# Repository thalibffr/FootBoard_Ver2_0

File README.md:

# Footboard ICHIRO Ver2.0

New Board Design for Foot Pressure of humanoid robot ICHIRO ITS

In this new design analog sensor data readings use ads1262

[Top view]

[Bottom view]

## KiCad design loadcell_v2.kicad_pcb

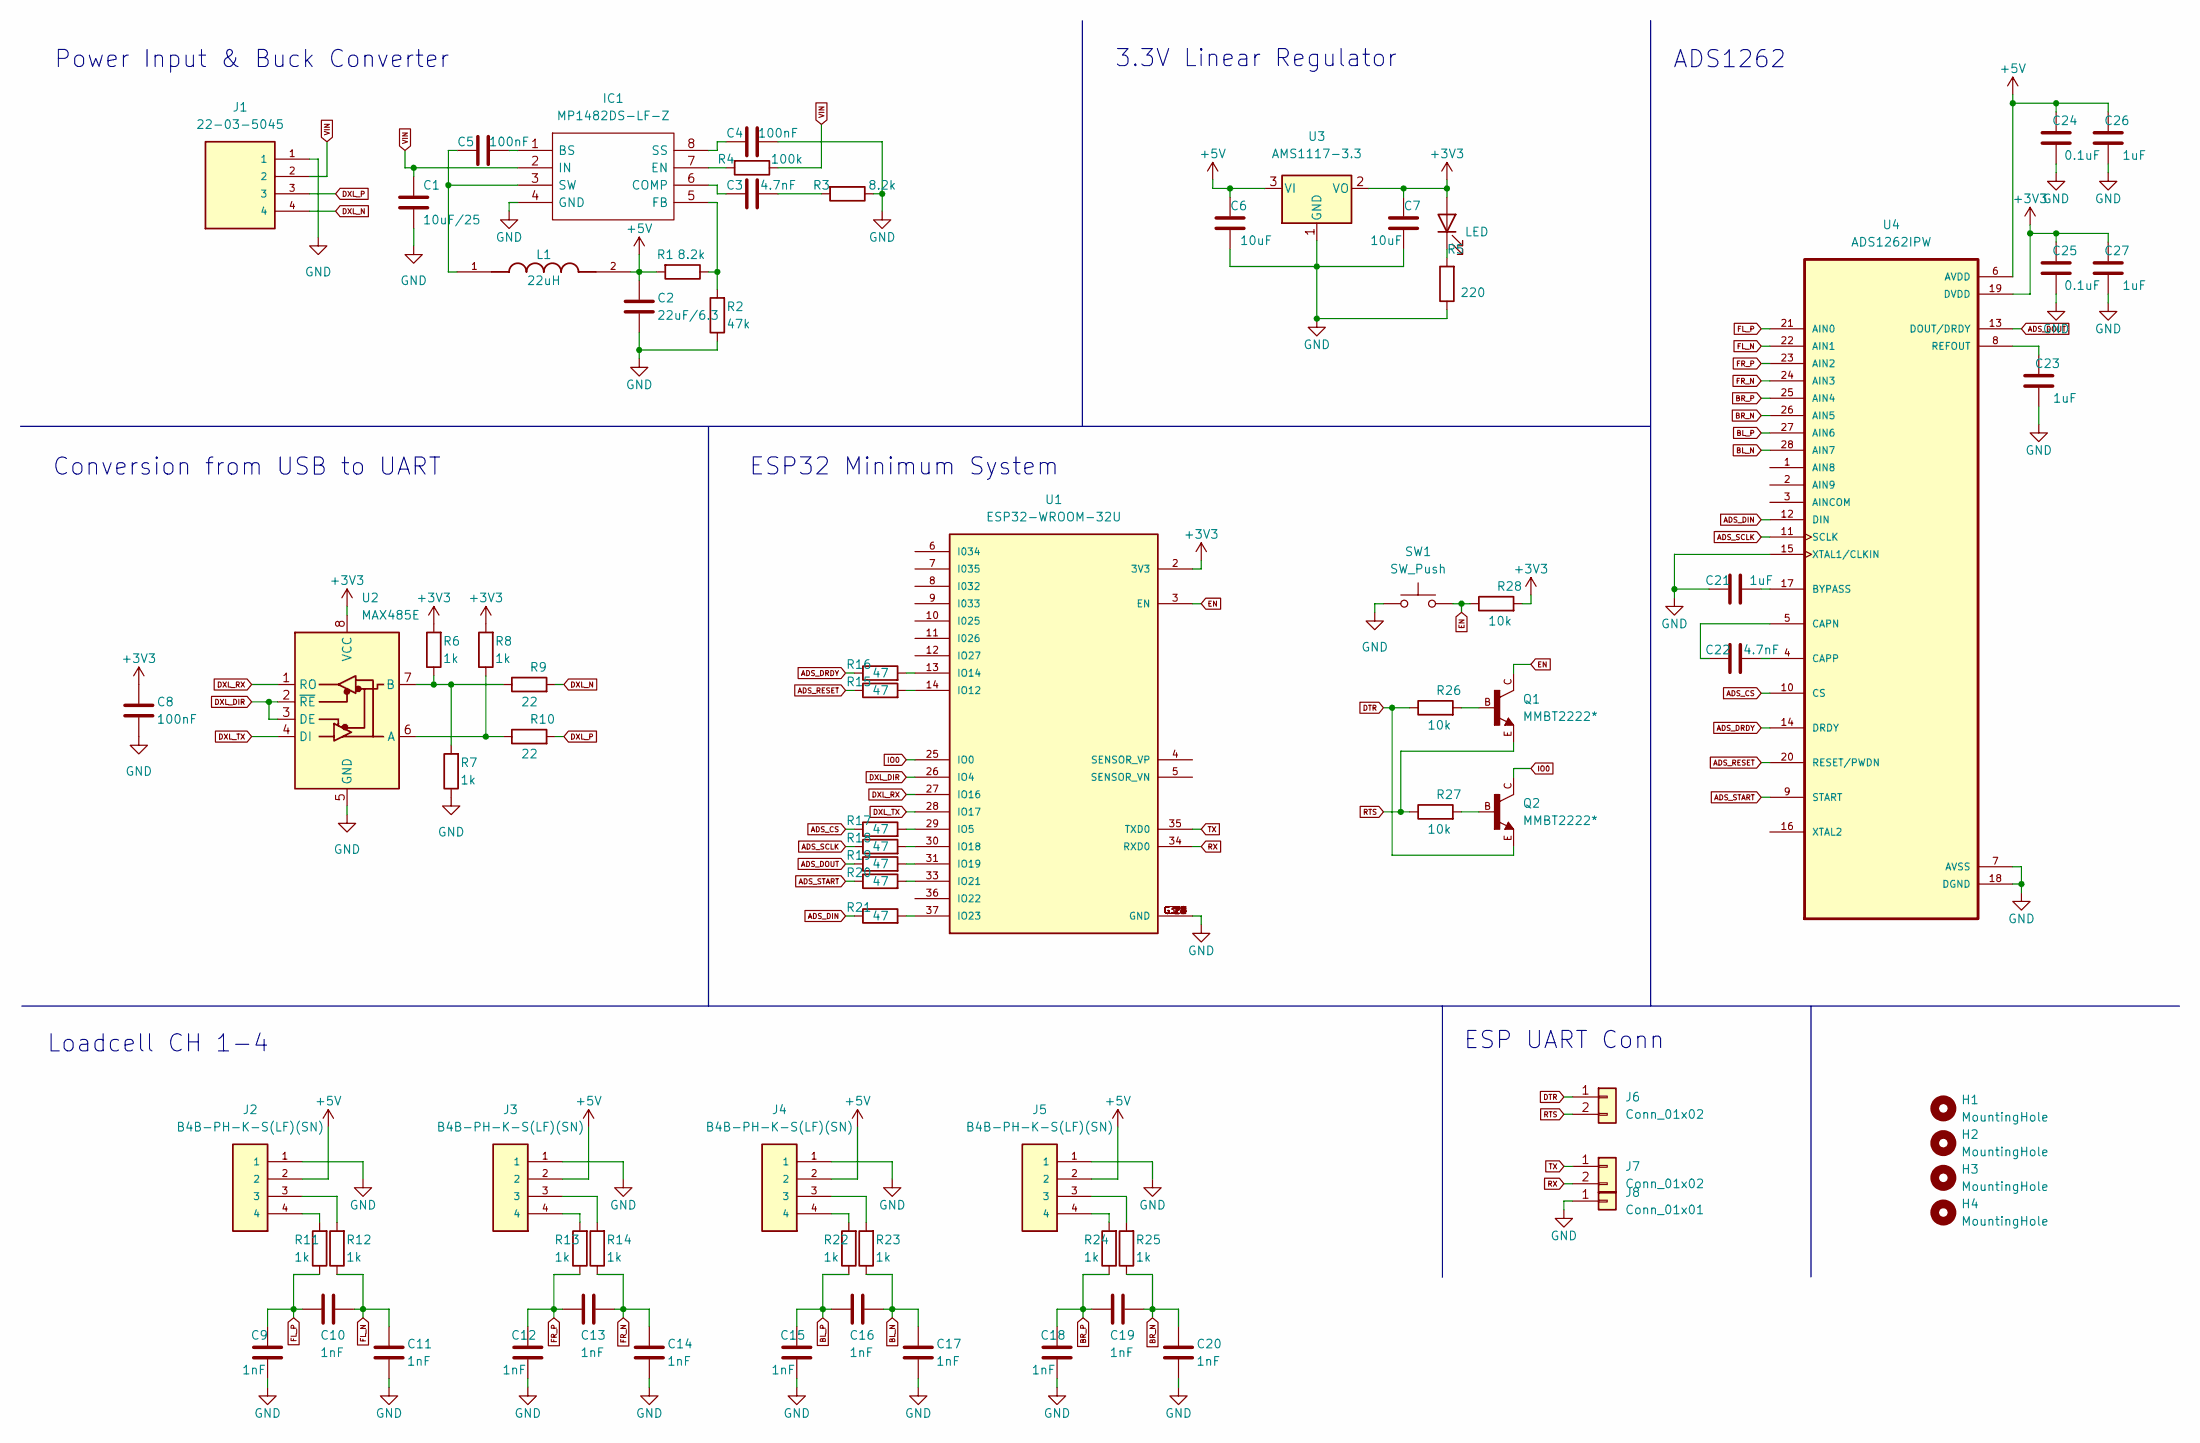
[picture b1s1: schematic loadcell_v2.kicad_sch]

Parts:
C1: 10uF/25; C_0805_2012Metric
C2: 22uF/6.3; C_0805_2012Metric
C3, C22: 4.7nF; C_0805_2012Metric
C4, C5, C8: 100nF; C_0805_2012Metric
C6, C7: 10uF; C_0805_2012Metric
C9, C10, C11, C12, C13, C14, C15, C16, C17, C18, C19, C20: 1nF; C_0805_2012Metric
C21, C23, C26, C27: 1uF; C_0805_2012Metric
C24, C25: 0.1uF; C_0805_2012Metric
D1: LED; LED_0805_2012Metric
H1, H2, H3, H4: MountingHole; MountingHole_3mm
IC1: MP1482DS-LF-Z; SOIC127P600X175-8N; Manufacturer_Part_Number MP1482DS-LF-Z; Mouser Part Number 946-MP1482DSLFZ
J1: 22-03-5045; MOLEX_22-03-5045; PARTREV B
J2, J3, J4, J5: B4B-PH-K-S(LF)(SN); JST_B4B-PH-K-S(LF)(SN)
J6, J7: Conn_01x02; PinHeader_1x02_P2.54mm_Vertical
J8: Conn_01x01; PinHeader_1x01_P2.54mm_Vertical
L1: 22uH; IND_VLS6045EX-3R3N; PARTREV N/A
Q1, Q2: MMBT2222*; SOT23-BEC
R1, R3: 8.2k; R_0805_2012Metric
R2: 47k; R_0805_2012Metric
R4: 100k; R_0805_2012Metric
R5: 220; R_0805_2012Metric
R6, R7, R8, R11, R12, R13, R14, R22, R23, R24, R25: 1k; R_0805_2012Metric
R9, R10: 22; R_0805_2012Metric
R15, R16, R17, R18, R19, R20, R21: 47; R_0805_2012Metric
R26, R27, R28: 10k; R_0805_2012Metric
SW1: SW_Push; SW_SPST_CK_RS282G05A3
U1: ESP32-WROOM-32U; XCVR_ESP32-WROOM-32U; PARTREV V1.9
U2: MAX485E; SOIC127P600X175-8N
U3: AMS1117-3.3; SOT229P700X180-4N
U4: ADS1262IPW; SOP65P640X120-28N

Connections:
+3V3: C7.2, C8.2, C25.2, C27.2, D1.2 (A), R6.2, R8.2, R28.2, U1.2 (3V3), U2.8 (VCC), U3.2 (VO), U4.19 (DVDD)
+5V: C2.2, C6.2, C24.2, C26.2, J2.2, J3.2, J4.2, J5.2, L1.2, R1.2, U3.3 (VI), U4.6 (AVDD)
ADS_CS: R17.1, U4.10 (CS)
ADS_DIN: R21.1, U4.12 (DIN)
ADS_DOUT: R19.1, U4.13 (DOUT/DRDY)
ADS_DRDY: R16.1, U4.14 (DRDY)
ADS_RESET: R15.1, U4.20 (RESET/PWDN)
ADS_SCLK: R18.1, U4.11 (SCLK)
ADS_START: R20.1, U4.9 (START)
BL_N: C16.2, C17.2, R23.1, U4.28 (AIN7)
BL_P: C15.2, C16.1, R22.1, U4.27 (AIN6)
BR_N: C19.2, C20.2, R25.1, U4.26 (AIN5)
BR_P: C18.2, C19.1, R24.1, U4.25 (AIN4)
DTR: J6.1, Q2.E, R26.1; also elsewhere on the board
DXL_DIR: U1.26 (IO4), U2.2 (~RE), U2.3 (DE)
DXL_N: J1.4, R9.2
DXL_P: J1.3, R10.2
DXL_RX: U1.27 (IO16), U2.1 (RO)
DXL_TX: U1.28 (IO17), U2.4 (DI)
EN: Q1.C, R28.1, SW1.2, U1.3 (EN)
FL_N: C10.2, C11.2, R12.1, U4.22 (AIN1)
FL_P: C9.2, C10.1, R11.1, U4.21 (AIN0)
FR_N: C13.2, C14.2, R14.1, U4.24 (AIN3)
FR_P: C12.2, C13.1, R13.1, U4.23 (AIN2)
GND: C1.2, C2.1, C4.1, C6.1, C7.1, C8.1, C9.1, C11.1, C12.1, C14.1, C15.1, C17.1, C18.1, C20.1, C21.1, C23.1, C24.1, C25.1, C26.1, C27.1, IC1.4 (GND), J1.1, J2.1, J3.1, J4.1, J5.1, J8.1, R2.1, R3.1, R5.1, R7.1, SW1.1, U1.1 (GND), U1.38 (GND), U1.G.11 (GND), U1.G.12 (GND), U1.G.13 (GND), U1.G.14 (GND), U1.G.15 (GND), U1.G.16 (GND), U1.G.17 (GND), U1.G.18 (GND), U1.G.19 (GND), U1.G.20 (GND), U1.G.21 (GND), U1.G.22 (GND), U2.5 (GND), U3.1 (GND), U4.7 (AVSS), U4.15 (XTAL1/CLKIN), U4.18 (DGND)
IO0: Q2.C, U1.25 (IO0)
unnamed: C3.1, R3.2
unnamed: C3.2, IC1.6 (COMP)
unnamed: C4.2, IC1.8 (SS)
unnamed: C5.1, IC1.1 (BS)
unnamed: C5.2, IC1.3 (SW), L1.1
unnamed: C21.2, U4.17 (BYPASS)
unnamed: C22.1, U4.4 (CAPP)
unnamed: C22.2, U4.5 (CAPN)
unnamed: C23.2, U4.8 (REFOUT)
unnamed: D1.1 (K), R5.2
unnamed: IC1.5 (FB), R1.1, R2.2
unnamed: IC1.7 (EN), R4.2
unnamed: J2.3, R12.2
unnamed: J2.4, R11.2
unnamed: J3.3, R14.2
unnamed: J3.4, R13.2
unnamed: J4.3, R23.2
unnamed: J4.4, R22.2
unnamed: J5.3, R25.2
unnamed: J5.4, R24.2
unnamed: Q1.B, R26.2
unnamed: Q2.B, R27.2
unnamed: R6.1, R7.2, R9.1, U2.7 (B)
unnamed: R8.1, R10.1, U2.6 (A)
unnamed: R15.2, U1.14 (IO12)
unnamed: R16.2, U1.13 (IO14)
unnamed: R17.2, U1.29 (IO5)
unnamed: R18.2, U1.30 (IO18)
unnamed: R19.2, U1.31 (IO19)
unnamed: R20.2, U1.33 (IO21)
unnamed: R21.2, U1.37 (IO23)
RTS: J6.2, Q1.E, R27.1; also elsewhere on the board
RX: J7.2, U1.34 (RXD0); also elsewhere on the board
TX: J7.1, U1.35 (TXD0); also elsewhere on the board
VIN: C1.1, IC1.2 (IN), J1.2, R4.1

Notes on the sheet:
3.3V Linear Regulator
Loadcell CH 1-4
Power Input & Buck Converter
ESP32 Minimum System
Conversion from USB to UART
ADS1262
ESP UART Conn

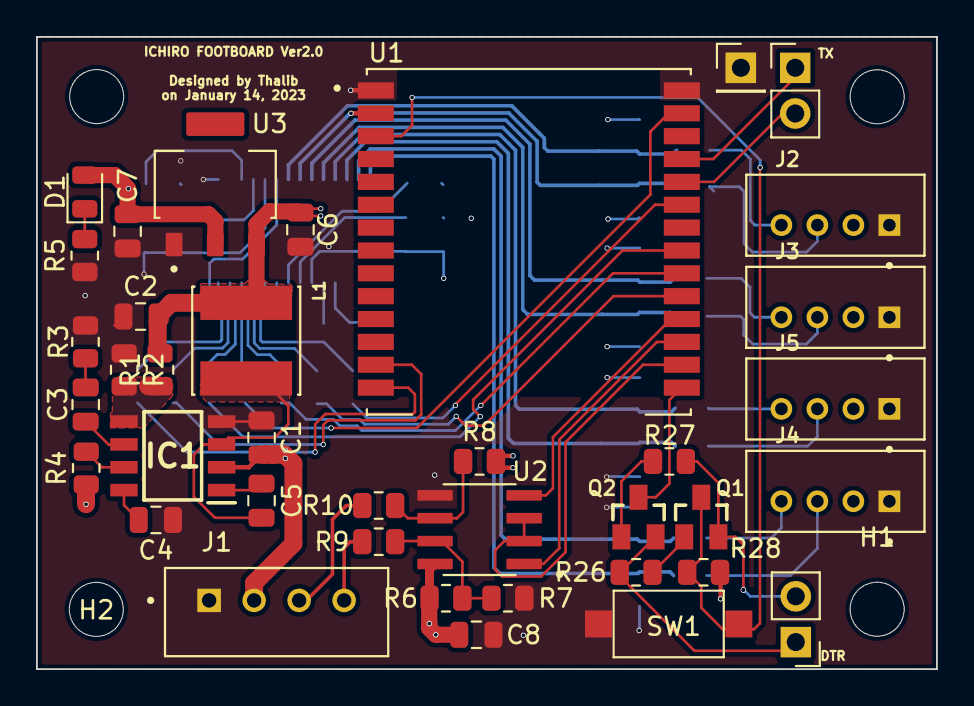
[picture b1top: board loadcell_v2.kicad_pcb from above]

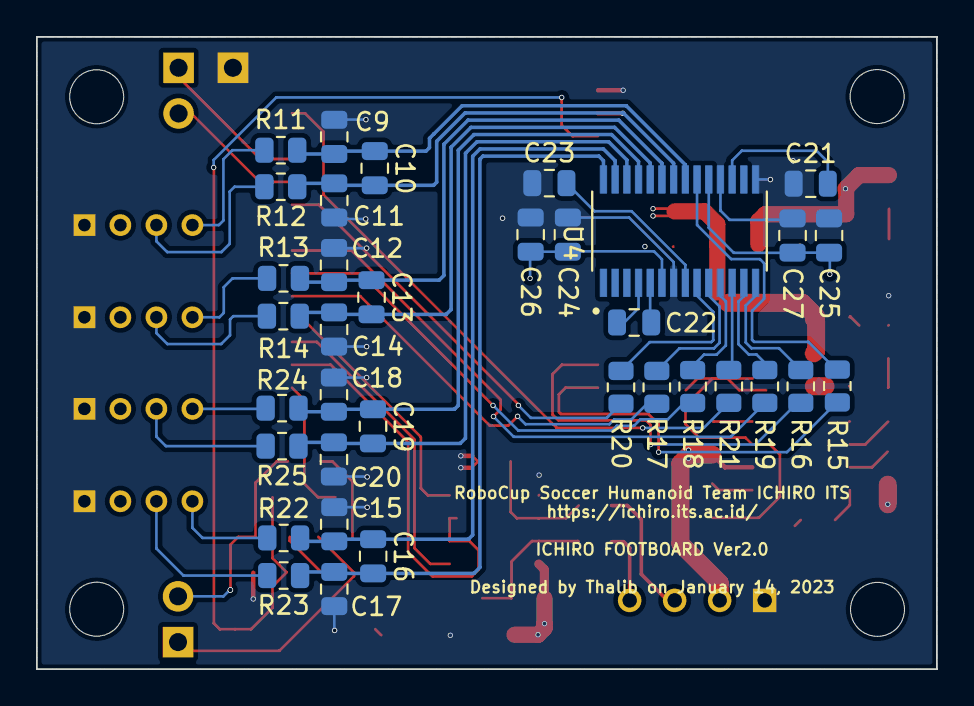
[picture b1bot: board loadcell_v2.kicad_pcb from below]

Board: 4 copper layers, 50.0 x 35.1 mm, 77 parts (35 on the bottom side), 61 nets.

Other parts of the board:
DTR: Conn_01x02; PinHeader_1x02_P2.54mm_Vertical
TX: Conn_01x02; PinHeader_1x02_P2.54mm_Vertical

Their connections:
DTR: DTR.1; also elsewhere on the board
RTS: DTR.2; also elsewhere on the board
RX: TX.2; also elsewhere on the board
TX: TX.1; also elsewhere on the board

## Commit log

2023-01-26 Create tes
2023-01-26 add file 3d FootBoard Ver2.0
2023-01-28 add 3d board imagee
2023-01-31 add schematic pdf
2023-01-31 add sch & brd file
